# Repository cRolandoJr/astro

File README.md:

# Astro 🤖

Robot compañero de escritorio: una **cara expresiva** que entiende lo que le decís,
te **responde con voz** y **actúa en la laptop** (abrir apps, media, ventanas…).
El cerebro vive en la PC (daemon en Go); el cuerpo es un ESP32 con pantalla, brazos y parlante.

> Proyecto personal / de aprendizaje (Go, embebido, NixOS/Hyprland). En diseño — arranca por software.

## Estado

- ✅ Diseño y arquitectura definidos
- ✅ Cara y 13 expresiones (dibujadas por primitivas)
- 🔜 **Fase A** (en PC, sin hardware): cara en pantalla + escribís un comando → hace la acción + responde
- ⏳ Voz (Whisper + Piper) · LLM · hardware ESP32

## Estructura

```
arquitectura.md        — arquitectura del asistente + roadmap por fases
guia-armado.md         — cómo armar el robot físico paso a paso
compra-final.md        — lista de compra única (componentes + precios)
mockup.html            — mockup visual (cara, expresiones, carcasas)
docs/specs/            — specs por fase (empezando por Fase A)
tutorial-original/     — tutorial base del que partió el proyecto + código nuestro (caras, firmware)
```

## Cómo funciona (resumen)

```
tu voz → Whisper (texto) → intención (reglas / LLM) → acción en la laptop
                                                     + voz de respuesta (Piper)
                                                     + cara/gesto (pantalla hoy, ESP32 después)
```

La IA **decide**; el código **ejecuta**. Las capacidades están acotadas a acciones curadas —
nada destructivo, sin shell arbitrario.

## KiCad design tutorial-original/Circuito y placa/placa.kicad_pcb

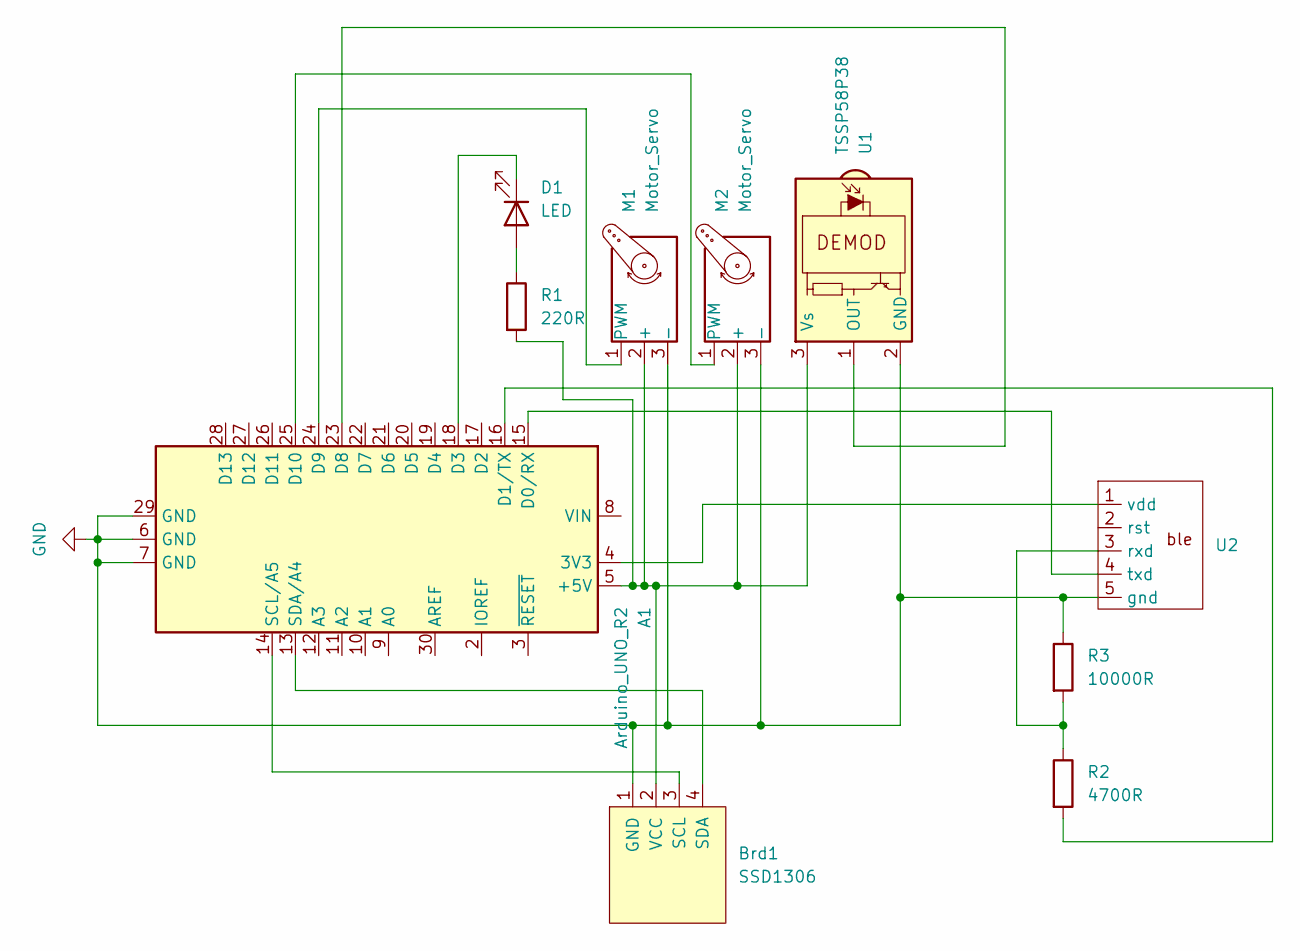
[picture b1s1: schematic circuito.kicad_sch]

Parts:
A1: Arduino_UNO_R2
Brd1: SSD1306; 128x64OLED
D1: LED; LED_D1.8mm_W3.3mm_H2.4mm
M1, M2: Motor_Servo; servo
R1: 220R; R_Axial_DIN0204_L3.6mm_D1.6mm_P7.62mm_Horizontal
R2: 4700R; R_Axial_DIN0204_L3.6mm_D1.6mm_P7.62mm_Horizontal
R3: 10000R; R_Axial_DIN0204_L3.6mm_D1.6mm_P7.62mm_Horizontal
U1: TSSP58P38; Vishay_MINICAST-3Pin
U2: blereyax

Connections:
GND: A1.6 (GND), A1.7 (GND), A1.29 (GND), Brd1.1 (GND), M1.3 (-), M2.3 (-), R3.1, U1.2 (GND), U2.5 (gnd)
unnamed: A1.4 (3V3), U2.1 (vdd)
unnamed: A1.5 (+5V), Brd1.2 (VCC), M1.2 (+), M2.2 (+), R1.2, U1.3 (Vs)
unnamed: A1.15 (D0/RX), U2.4 (txd)
unnamed: A1.16 (D1/TX), R2.2
unnamed: A1.18 (D3), D1.1 (K)
unnamed: A1.23 (D8), U1.1 (OUT)
unnamed: A1.24 (D9), M1.1 (PWM)
unnamed: A1.25 (D10), M2.1 (PWM)
unnamed: A1.14 (SCL/A5), Brd1.3 (SCL)
unnamed: A1.13 (SDA/A4), Brd1.4 (SDA)
unnamed: D1.2 (A), R1.1
unnamed: R2.1, R3.2, U2.3 (rxd)

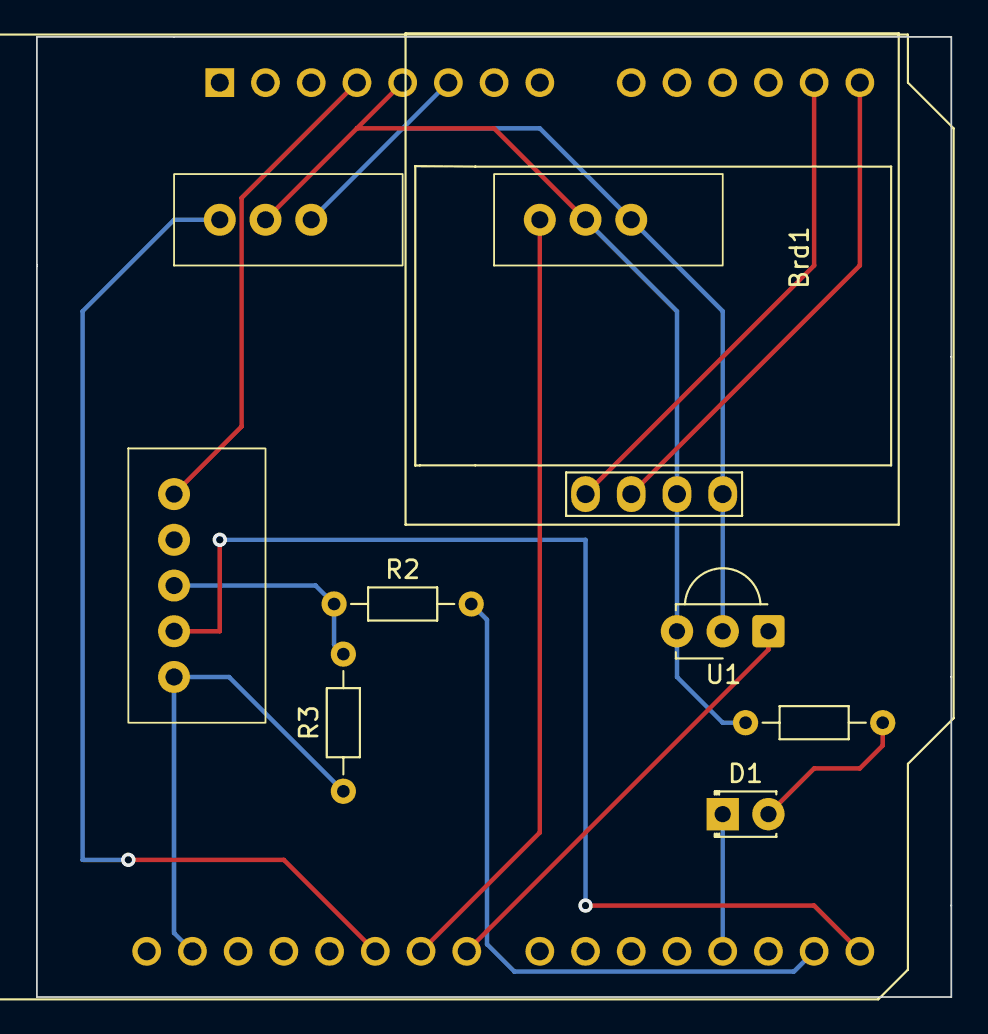
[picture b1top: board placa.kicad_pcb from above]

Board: 2 copper layers, 50.8 x 53.3 mm, 10 parts (0 on the bottom side), 13 nets.
